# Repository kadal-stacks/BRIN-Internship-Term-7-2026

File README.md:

<!-- Official BRIN logo sourced from Wikimedia Commons; no AI-generated imagery is used. -->
<p align="center">
  
</p>

<h1 align="center">BRIN Internship | Term 7 · 2026</h1>

<p align="center">
  Catatan kerja dan hasil praktik di bidang embedded systems, firmware mikrokontroler, serta desain rangkaian dan PCB.
</p>

<p align="center">

</p>

---

## Tentang repositori

Repositori ini mengumpulkan pekerjaan teknis selama **Magang BRIN Term 7 (2026)**. Isinya berkembang melalui proyek KiCad untuk perancangan elektronik dan PCB, eksperimen program mikrokontroler, serta contoh firmware untuk latihan dan pengujian.

Struktur dibuat mengikuti kelompok pekerjaan agar file desain, source code, dan library pendukung tetap berada dekat dengan proyek masing-masing. Status setiap desain perlu dinilai dari file dan hasil verifikasi yang tersedia; keberadaan file proyek tidak otomatis berarti desain sudah tervalidasi atau siap fabrikasi.

## Ruang lingkup

### 1. Desain elektronik dan PCB dengan KiCad

| Folder | Isi |
| --- | --- |
| [`KiCAD/ATMega16-STM32 BP Adapter`](KiCAD/ATMega16-STM32%20BP%20Adapter) | Proyek adapter/pemetaan koneksi ATmega16 ke board STM32, dengan varian **SMD** dan **THT**. Berisi project, schematic, layout PCB, dan file pendukung yang tersedia. |
| [`KiCAD/Howland-VCCS`](KiCAD/Howland-VCCS) | Proyek rangkaian Howland Voltage-Controlled Current Source menggunakan TL072, dengan beberapa varian footprint/perakitan. |
| [`KiCAD/Impedance-meter2D_Main Board`](KiCAD/Impedance-meter2D_Main%20Board) | Folder proyek untuk main board impedance meter. Kelengkapan desain dapat berbeda dari proyek lainnya. |
| [`KiCAD/Part Lib/Kicad-STM32`](KiCAD/Part%20Lib/Kicad-STM32) | Library simbol, footprint, dan model 3D untuk modul STM32 **Blue Pill** dan **Black Pill**. Lihat README di dalam folder untuk rincian library. |
| [`KiCAD/Folder Tugas`](KiCAD/Folder%20Tugas) | Folder untuk materi/tugas KiCad. |

Format yang umum dijumpai antara lain `.kicad_pro` (project), `.kicad_sch` (schematic), `.kicad_pcb` (PCB layout), `.kicad_sym` (symbol library), dan `.kicad_mod` (footprint).

### 2. Firmware dan eksperimen mikrokontroler

| Lokasi | Isi |
| --- | --- |
| [`Program_MCU/AVR/AVR Atmega 328p - Arduino UNO R3`](Program_MCU/AVR/AVR%20Atmega%20328p%20-%20Arduino%20UNO%20R3) | Eksperimen pada ATmega328P/Arduino Uno R3, termasuk proyek ADC dan program LED non-blocking. |
| [`LED-Berjalan.cpp`](LED-Berjalan.cpp) | Contoh program LED berjalan. |
| [`Non-blocking using Multi LED.cpp`](Non-blocking%20using%20Multi%20LED.cpp) | Contoh pengaturan beberapa pola LED tanpa bergantung pada jeda blocking di loop utama. |

Sebagian proyek firmware memiliki `platformio.ini` dan dapat dibuka sebagai proyek PlatformIO. Untuk source code yang berdiri sendiri, pilih board, framework, pin, serta konfigurasi build yang sesuai sebelum mengompilasi.

## Deliverable PCB dan firmware terbaru

### PCB dengan paket Gerber dan gambar area

| Board | Luas outline | Dokumentasi |
| --- | ---: | --- |
| ATmega16–STM32 Adapter SMD | 1,450.75 mm² (14.5075 cm²) | [Gerber, drill, dan gambar area](KiCAD/ATMega16-STM32%20BP%20Adapter/ATMega16-STM32%20BP%20Adapter_SMD/README.md) |
| Howland VCCS TL072 THT | 3,506.24 mm² (35.0624 cm²) | [Gerber, drill, dan gambar area](KiCAD/Howland-VCCS/Howland-VCCS-TL072/README.md) |
| Howland VCCS TL072 SMD/hybrid | 618.85 mm² (6.1885 cm²) | [Gerber, drill, dan gambar area](KiCAD/Howland-VCCS/Howland-VCCS-TL072_SMD/Howland-VCCS-TL072_SMD/README.md) |

Luas dihitung dari outline `Edge.Cuts` pada file PCB sebagai rounded rectangle, bukan dari perkiraan visual. Board Raspberry Pi Zero Dev Board juga memiliki ukuran outline yang didokumentasikan, tetapi Gerber belum tersedia.

### Firmware AD9833

- [VCCS–AD9833 Frequency Controller (Arduino Nano)](Program_MCU/AVR/AVR%20Atmega%20328p%20-%20Arduino%20Nano/VCCS-AD9833%20Regulator/README.md)
- [Salinan di folder Arduino UNO R3](Program_MCU/AVR/AVR%20Atmega%20328p%20-%20Arduino%20UNO%20R3/VCCS%20-%20AD9833%20Regulator/README.md). Catatan: konfigurasi `platformio.ini` saat ini masih memilih board Nano.

## Alur kerja

Alur berikut merangkum cara menavigasi dan melanjutkan pekerjaan di repositori ini. Langkah verifikasi tetap perlu disesuaikan dengan proyek dan hardware yang digunakan.

1. **Pilih proyek yang relevan.** Buka folder di `KiCAD/` untuk pekerjaan desain atau `Program_MCU/` untuk eksperimen firmware.
2. **Buka file proyek utama.** Untuk KiCad, buka file `.kicad_pro` di folder proyek agar hubungan schematic, PCB, dan library lokal lebih mudah dipertahankan.
3. **Periksa keterkaitan desain.** Pastikan nomor pin, nama net, simbol, footprint, orientasi konektor, ukuran mekanik, dan tegangan logika sesuai datasheet serta modul fisik. Hal ini sangat penting untuk adapter ATmega16–STM32.
4. **Verifikasi sebelum menganggap selesai.** Tinjau Electrical Rules Checker (ERC) untuk schematic dan Design Rules Checker (DRC) untuk PCB. Periksa hasil simulasi atau pengujian firmware jika tersedia. ERC/DRC yang bersih sendiri tidak menjamin rangkaian bekerja pada hardware.
5. **Simpan perubahan secara terstruktur.** Pertahankan file yang dibutuhkan proyek, hindari memasukkan file lock atau file sementara editor, lalu commit perubahan dengan pesan yang menjelaskan lingkup pekerjaan.

## Referensi visual

Gambar di bawah merupakan tangkapan layar asli dari dokumentasi KiCad, digunakan sebagai referensi antarmuka schematic dan PCB editor, bukan sebagai klaim bahwa gambar tersebut adalah hasil desain proyek ini.

<p align="center">

</p>

## Galeri perangkat keras: foto referensi non-AI

Foto berikut berasal dari halaman produk/vendor atau aset foto yang sudah tersimpan di repository. Gambar membantu mengenali komponen, **bukan bukti bahwa board pada proyek ini sudah dirakit atau diuji**.

<p align="center">

</p>

<sub>Sumber foto: <a href="https://www.mikroe.com/atmega16">MikroE ATmega16</a>, aset <a href="KiCAD/Part%20Lib/Kicad-STM32/README.md">Blue Pill repository</a>, <a href="https://www.ti.com/product/TL072">TI TL072 / foto paket IC dari pemasok</a>, <a href="https://wholesale.pimoroni.com/en-eu/products/adafruit-bmp280-i2c-or-spi-barometric-pressure-altitude-sensor">modul BMP280 dari pemasok</a>, dan <a href="https://laelectronica.com.gt/arduino-uno-rev3">foto Arduino Uno R3</a>. Foto TL072 yang ditampilkan adalah paket DIP-8; periksa footprint proyek sebelum membeli komponen.</sub>

## Memulai

- **KiCad:** instal KiCad, lalu buka file `.kicad_pro` dari folder proyek yang akan dikerjakan.
- **Firmware:** untuk proyek yang memiliki `platformio.ini`, gunakan VS Code dengan ekstensi PlatformIO atau PlatformIO CLI. Pastikan board/framework cocok dengan konfigurasi proyek.
- **Hardware:** sebelum upload firmware atau memberi daya, cocokkan wiring dan level tegangan dengan datasheet serta lakukan pemeriksaan dasar untuk menghindari kerusakan komponen.

## Catatan status dan akurasi

Repositori ini merupakan arsip kerja yang berkembang. Skema, mapping pin, footprint, routing, pengaturan panel, dan source code perlu diverifikasi terhadap versi tool, datasheet komponen, hardware aktual, serta persyaratan manufaktur. Jangan menganggap desain siap produksi hanya berdasarkan visual layout atau status file yang sudah di-commit.

## Sumber gambar dan aset

- **Logo BRIN:** karya resmi Badan Riset dan Inovasi Nasional; ditautkan dari [Wikimedia Commons](https://commons.wikimedia.org/wiki/File:LOGO_BRIN_NEW.jpg), yang mencatat sumber dan status domain publik di Indonesia.
- **Tangkapan layar KiCad:** [KiCad 8 release article](https://www.kicad.org/blog/2024/02/Version-8.0.0-Released/) dan [dokumentasi PCB Editor KiCad](https://docs.kicad.org/9.0/it/pcbnew/pcbnew.html).
- **Library STM32:** lihat [README library lokal](KiCAD/Part%20Lib/Kicad-STM32/README.md) untuk detail simbol, footprint, model 3D, dan konteks sumbernya.

<p align="center">
  <sub>Logo BRIN digunakan untuk menunjukkan konteks kegiatan magang. Repositori ini tidak menyatakan dirinya sebagai repositori resmi BRIN.</sub>
</p>

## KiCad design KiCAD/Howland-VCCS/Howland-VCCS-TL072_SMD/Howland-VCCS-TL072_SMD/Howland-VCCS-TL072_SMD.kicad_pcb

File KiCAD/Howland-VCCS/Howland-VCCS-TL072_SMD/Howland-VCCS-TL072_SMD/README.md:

<p align="center">
  
</p>

# Howland VCCS with TL072 (SMD / Hybrid)

Project KiCad untuk varian Howland VCCS dengan jaringan resistor SMD 0805. Schematic terbaru berbeda dari revisi lama: kini memakai R1–R4 = 100 kΩ, R5 = 150 Ω, dan RV1 = 1 kΩ.

## Komponen dari schematic

| Ref. | Komponen | Nilai / footprint |
| --- | --- | --- |
| U1 | Dual op-amp TL072 | **DIP-8 THT** |
| R1–R4 | Resistor | 100 kΩ, SMD 0805 |
| R5 | Resistor | 150 Ω, SMD 0805 |
| RV1 | Potensiometer trimmer | 1 kΩ, Bourns 3296W vertical THT |
| J4 | Pin header 1×6 | Pitch 2.54 mm, THT |
| H1–H2 | Mounting hole | M2.2 / M2 |
| Net labels | Id+, Id-, Out | Label antarmuka sinyal |

Desain ini **hybrid**, bukan full-SMD, karena U1, RV1, dan J4 masih memakai footprint through-hole. Schematic yang terbaru tidak lagi menunjukkan R6/R7, C1/C2, atau solder jumper JP1/JP2 yang tercantum di dokumentasi versi sebelumnya.

Secara fungsi, topologi Howland ditujukan untuk menghasilkan arus beban yang dikendalikan sinyal tegangan. Rasio resistor dan toleransinya mempengaruhi akurasi. Verifikasi supply VCC/VEE, swing output TL072, compliance voltage, dan koneksi beban sebelum uji.

## Dimensi dan luas board

| Parameter | Nilai |
| --- | ---: |
| Lebar bounding outline | 27.078 mm |
| Tinggi bounding outline | 22.886 mm |
| Radius sudut | 1.00 mm |
| Luas bounding rectangle | 619.71 mm² |
| Koreksi empat sudut membulat | 0.86 mm² |
| **Luas bidang PCB aktual** | **618.85 mm²** |
| **Konversi** | **6.1885 cm²** |

Luas dihitung dari rounded outline pada layer `Edge.Cuts` menggunakan `A = W × H − (4 − π)r²`.

## Paket Gerber dan drill

**Status: Gerber dan drill tersedia.**

[Unduh paket Gerber ZIP](Howland-VCCS-TL072-SMD-Gerber.zip)

Layer individual:
- Copper: [F_Cu](Howland-VCCS-TL072_SMD-F_Cu.gbr), [B_Cu](Howland-VCCS-TL072_SMD-B_Cu.gbr)
- Solder mask: [F_Mask](Howland-VCCS-TL072_SMD-F_Mask.gbr), [B_Mask](Howland-VCCS-TL072_SMD-B_Mask.gbr)
- Paste: [F_Paste](Howland-VCCS-TL072_SMD-F_Paste.gbr), [B_Paste](Howland-VCCS-TL072_SMD-B_Paste.gbr)
- Silkscreen: [F_Silkscreen](Howland-VCCS-TL072_SMD-F_Silkscreen.gbr), [B_Silkscreen](Howland-VCCS-TL072_SMD-B_Silkscreen.gbr)
- Board profile: [Edge_Cuts](Howland-VCCS-TL072_SMD-Edge_Cuts.gbr)
- Drill: [PTH](Howland-VCCS-TL072_SMD-PTH.drl), [NPTH](Howland-VCCS-TL072_SMD-NPTH.drl)
- Job metadata: [Gerber job](Howland-VCCS-TL072_SMD-job.gbrjob)

Gerber dibuat dengan KiCad 10.0.5 pada 13 November 2026.

## File project

- `Howland-VCCS-TL072_SMD.kicad_pro`
- `Howland-VCCS-TL072_SMD.kicad_sch`
- `Howland-VCCS-TL072_SMD.kicad_pcb`

Sebelum fabrikasi, pastikan nilai/footprint sesuai schematic terbaru, khususnya footprint U1 DIP-8 dan trimmer THT. Jalankan ERC/DRC lagi apabila ada perubahan schematic, footprint, atau layout.

---

[README varian parent](../README.md) · [README Howland VCCS](../../README.md)

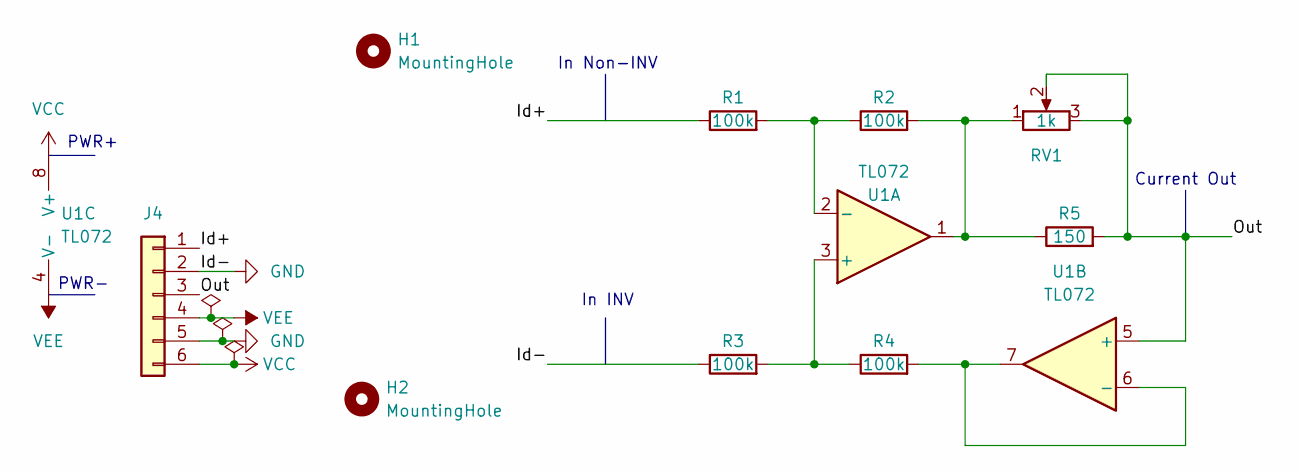
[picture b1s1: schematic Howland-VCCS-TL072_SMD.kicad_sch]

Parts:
H1, H2: MountingHole; MountingHole_2.2mm_M2
J4: Conn_01x06; PinHeader_1x06_P2.54mm_Vertical
R1, R2, R3, R4: 100k; R_0805_2012Metric
R5: 150; R_0805_2012Metric
RV1: 1k; Potentiometer_Bourns_3296W_Vertical
U1: TL072; DIP-8_W7.62mm

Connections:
/Id+: J4.1, R1.1
/Out: J4.3, R5.2, RV1.2, RV1.3, U1.5 (+)
GND: J4.2, J4.5, R3.1
unnamed: R2.2, R5.1, RV1.1, U1.1
unnamed: R3.2, R4.1, U1.3 (+)
unnamed: R1.2, R2.1, U1.2 (-)
unnamed: R4.2, U1.6 (-), U1.7
VCC: J4.6, U1.8 (V+)
VEE: J4.4, U1.4 (V-)

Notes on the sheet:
In INV
In Non-INV
PWR-
Current Out
PWR+

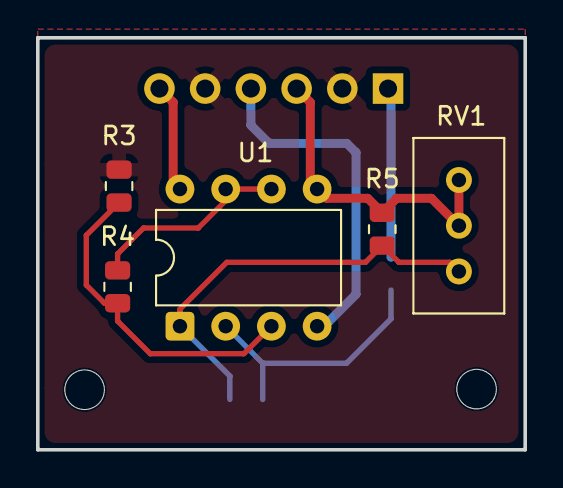
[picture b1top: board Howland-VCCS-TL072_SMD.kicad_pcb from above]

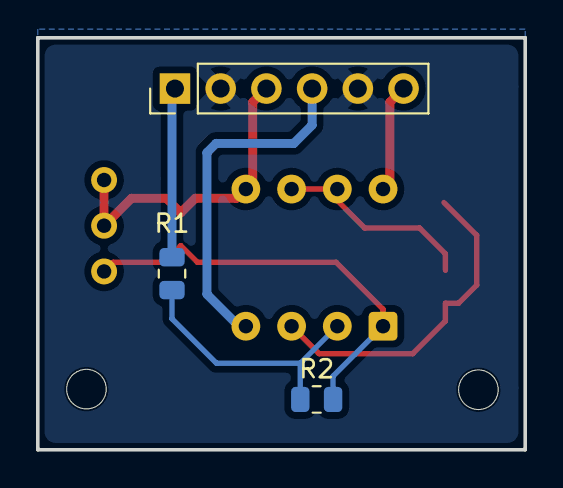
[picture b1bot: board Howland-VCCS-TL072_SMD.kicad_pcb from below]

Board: 2 copper layers, 27.1 x 22.9 mm, 10 parts (3 on the bottom side), 9 nets.

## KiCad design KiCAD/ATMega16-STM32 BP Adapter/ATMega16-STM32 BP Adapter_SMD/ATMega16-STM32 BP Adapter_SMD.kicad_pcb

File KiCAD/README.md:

<table align="center">
  <tr>
    <td align="center" valign="middle" width="33%">
      
    </td>
    <td align="center" valign="middle" width="33%">
      
    </td>
    <td align="center" valign="middle" width="33%">
      
    </td>
  </tr>
</table>
<p align="center"><sub>STM32 Blue Pill / Black Pill reference · Arm Cortex core depends on the exact MCU variant</sub></p>

# KiCad Projects

Folder ini menampung schematic, PCB layout, library komponen, dan paket manufaktur dari proyek instrumentasi selama magang.

## Proyek

| Proyek | Fungsi | Status file manufaktur | Area outline PCB |
| --- | --- | --- | ---: |
| [ATmega16–STM32 Adapter (SMD)](ATMega16-STM32%20BP%20Adapter/ATMega16-STM32%20BP%20Adapter_SMD/README.md) | Breakout dan routing pin ATmega16 ke header STM32 | Gerber + drill tersedia | **1,450.75 mm² / 14.5075 cm²** |
| [Howland VCCS TL072 (THT)](Howland-VCCS/Howland-VCCS-TL072/README.md) | Voltage-controlled current source berbasis TL072 | Gerber + drill tersedia | **3,506.24 mm² / 35.0624 cm²** |
| [Howland VCCS TL072 (SMD/hybrid)](Howland-VCCS/Howland-VCCS-TL072_SMD/Howland-VCCS-TL072_SMD/README.md) | Varian Howland dengan resistor SMD dan IC/op-amp THT | Gerber + drill tersedia | **618.85 mm² / 6.1885 cm²** |
| [Impedance Meter Main Board](Impedance-meter2D_Main%20Board/README.md) | Workspace main board impedance meter | File manufaktur belum tersedia di folder | Belum dihitung |
| [Part Libraries](Part%20Lib/README.md) | Symbol, footprint, dan model 3D | Library | — |
| [Raspberry Pi Zero Dev Board](RaspiZeroDevBoard/README.md) | Carrier board Raspberry Pi Zero dengan ADC eksternal, RTC, interface serial, RS-485, LCD, dan rail daya | PCB tersedia; Gerber belum ada | **19,581.96 mm² / 195.8196 cm²** |
| [VCCS 2 Buffer](Howland-VCCS/VCCS%202%20Buffer/README.md) | Workspace schematic buffer berbasis AD826ANZ dan TL082 | PCB masih stub; Gerber/area belum tersedia | Belum dihitung |

### Area board yang sudah dihitung

Dimensi diambil dari geometri `Edge.Cuts` pada file PCB dan dicocokkan dengan layer Gerber profile. Ketiga outline berbentuk persegi panjang dengan empat sudut membulat. Area dihitung sebagai:

`A = (W × H) − (4 − π)r²`

dengan `W` dan `H` sebagai ukuran bounding rectangle dan `r` sebagai radius sudut. Nilai ini adalah luas bidang outline PCB, bukan luas komponen atau bounding box tanpa koreksi sudut.

## Workflow manufaktur KiCad

1. Buka file `.kicad_pro` dari folder proyek.
2. Validasi schematic, footprint, nomor pad, konektor, dan net.
3. Jalankan ERC untuk schematic dan DRC untuk PCB.
4. Plot layer Gerber yang diperlukan dan generate file drill PTH/NPTH.
5. Periksa file `Edge_Cuts.gbr`, `*.gbrjob`, dan arsip ZIP sebelum dikirim ke manufaktur.

Paket Gerber yang tersedia ditautkan dari README masing-masing proyek. Jangan menggunakan file dari folder atau revisi berbeda sebagai satu paket produksi.

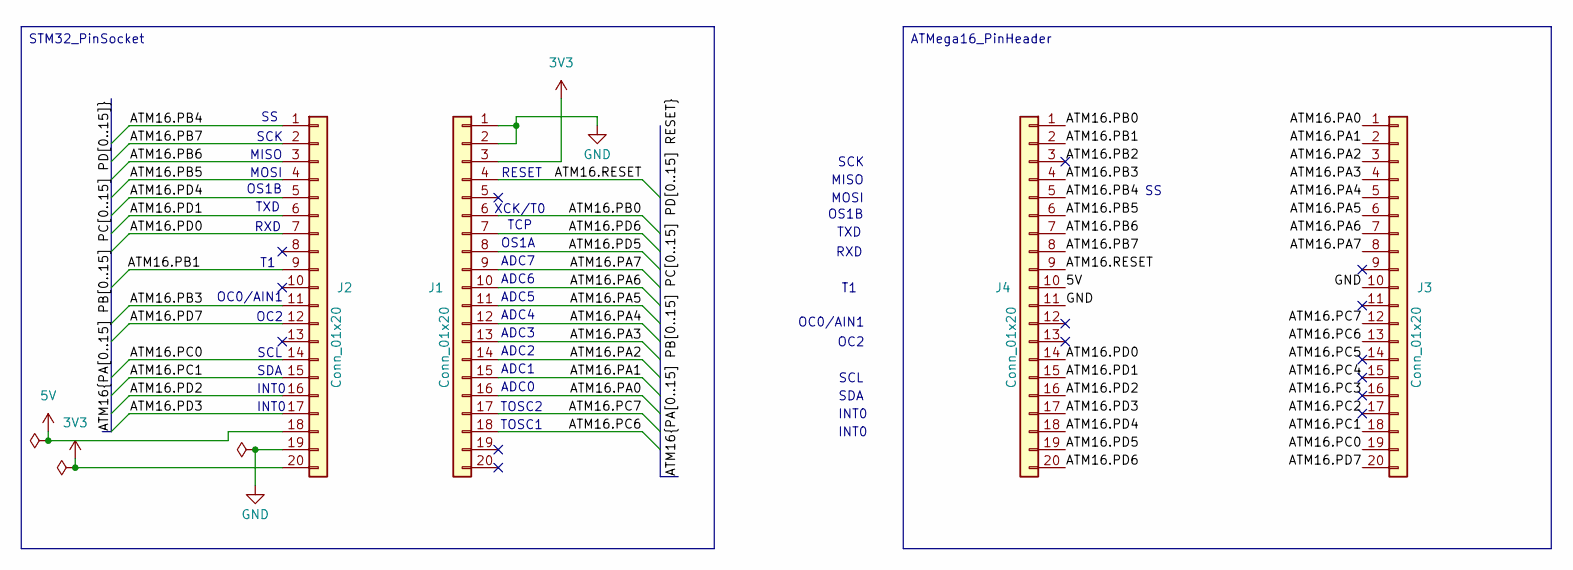
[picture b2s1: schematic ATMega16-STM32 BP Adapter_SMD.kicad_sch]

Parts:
J1: Conn_01x20; PinSocket_1x20_P2.54mm_Vertical_SMD_Pin1Right
J2: Conn_01x20; PinSocket_1x20_P2.54mm_Vertical_SMD_Pin1Left
J3: Conn_01x20; PinHeader_1x20_P2.54mm_Vertical_SMD_Pin1Right
J4: Conn_01x20; PinHeader_1x20_P2.54mm_Vertical_SMD_Pin1Left

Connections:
3V3: J1.3, J2.20
5V: J2.18, J4.10
/ATM16.PA0: J1.16, J3.1
/ATM16.PA1: J1.15, J3.2
/ATM16.PA2: J1.14, J3.3
/ATM16.PA3: J1.13, J3.4
/ATM16.PA4: J1.12, J3.5
/ATM16.PA5: J1.11, J3.6
/ATM16.PA6: J1.10, J3.7
/ATM16.PA7: J1.9, J3.8
/ATM16.PB0: J1.6, J4.1
/ATM16.PB1: J2.9, J4.2
/ATM16.PB2: J4.3
/ATM16.PB3: J2.11, J4.4
/ATM16.PB4: J2.1, J4.5
/ATM16.PB5: J2.4, J4.6
/ATM16.PB6: J2.3, J4.7
/ATM16.PB7: J2.2, J4.8
/ATM16.PC0: J2.14, J3.19
/ATM16.PC1: J2.15, J3.18
/ATM16.PC2: J3.17
/ATM16.PC3: J3.16
/ATM16.PC4: J3.15
/ATM16.PC5: J3.14
/ATM16.PC6: J1.18, J3.13
/ATM16.PC7: J1.17, J3.12
/ATM16.PD0: J2.7, J4.14
/ATM16.PD1: J2.6, J4.15
/ATM16.PD2: J2.16, J4.16
/ATM16.PD3: J2.17, J4.17
/ATM16.PD4: J2.5, J4.18
/ATM16.PD5: J1.8, J4.19
/ATM16.PD6: J1.7, J4.20
/ATM16.PD7: J2.12, J3.20
/ATM16.RESET: J1.4, J4.9
GND: J1.1, J1.2, J2.19, J3.10, J4.11

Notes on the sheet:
OC2
INT0
SCK
RXD
ADC7
RESET
OC0/AIN1
SDA
ADC1
ADC2
SCL
MOSI
TXD
TOSC2
ADC4
OS1A
OS1B
TOSC1
TCP
XCK/T0
MISO
ADC6
ADC5
ADC3
ADC0
ATMega16_PinHeader
STM32_PinSocket

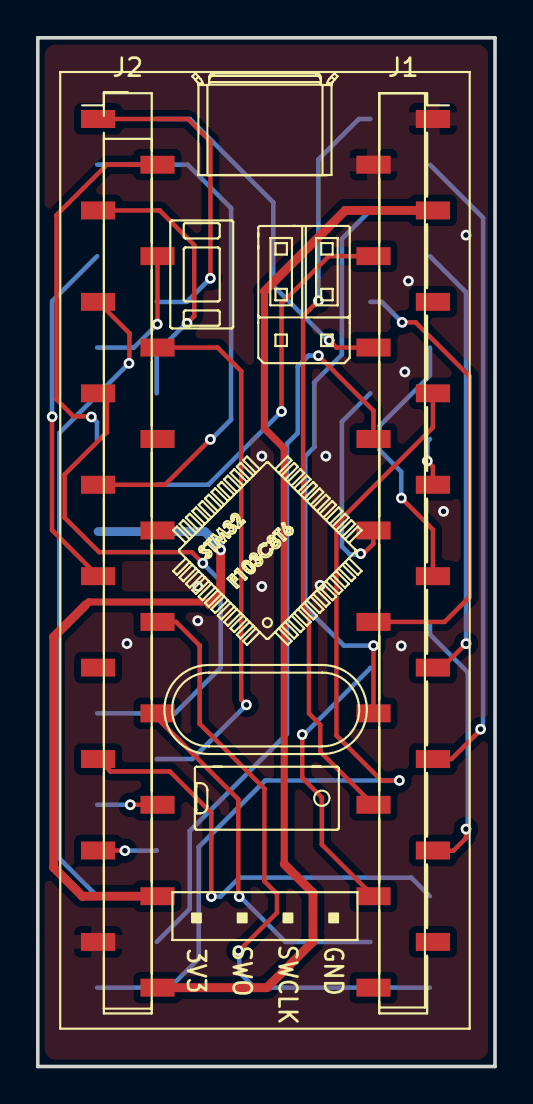
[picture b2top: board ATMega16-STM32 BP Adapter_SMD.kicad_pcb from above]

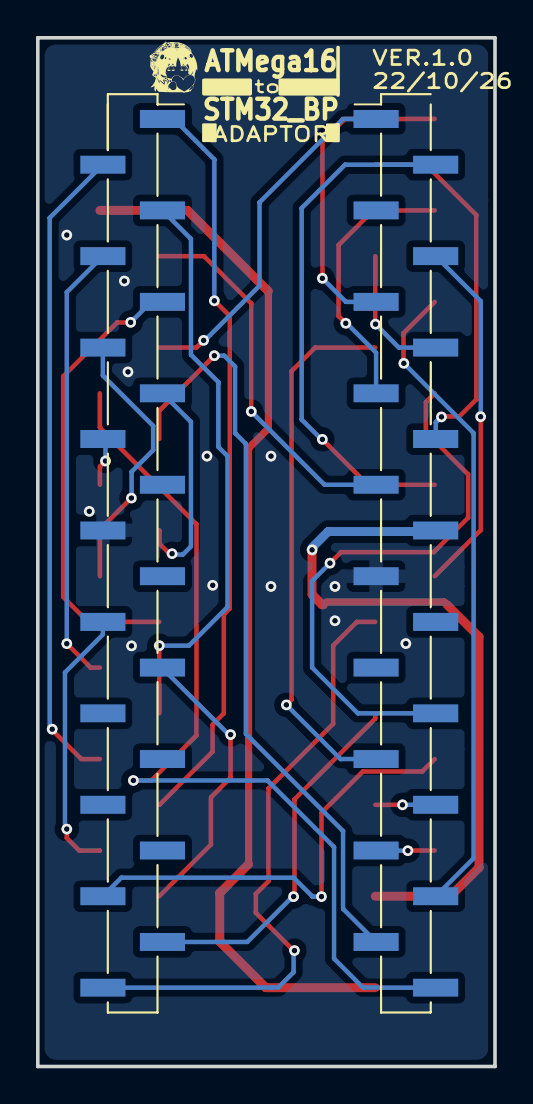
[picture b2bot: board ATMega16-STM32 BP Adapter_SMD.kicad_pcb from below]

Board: 2 copper layers, 25.4 x 57.1 mm, 5 parts (2 on the bottom side), 31 nets.

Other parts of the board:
U2: YAAJ_BluePill_Part_Like; BLUEPILL_SILKSCREEN

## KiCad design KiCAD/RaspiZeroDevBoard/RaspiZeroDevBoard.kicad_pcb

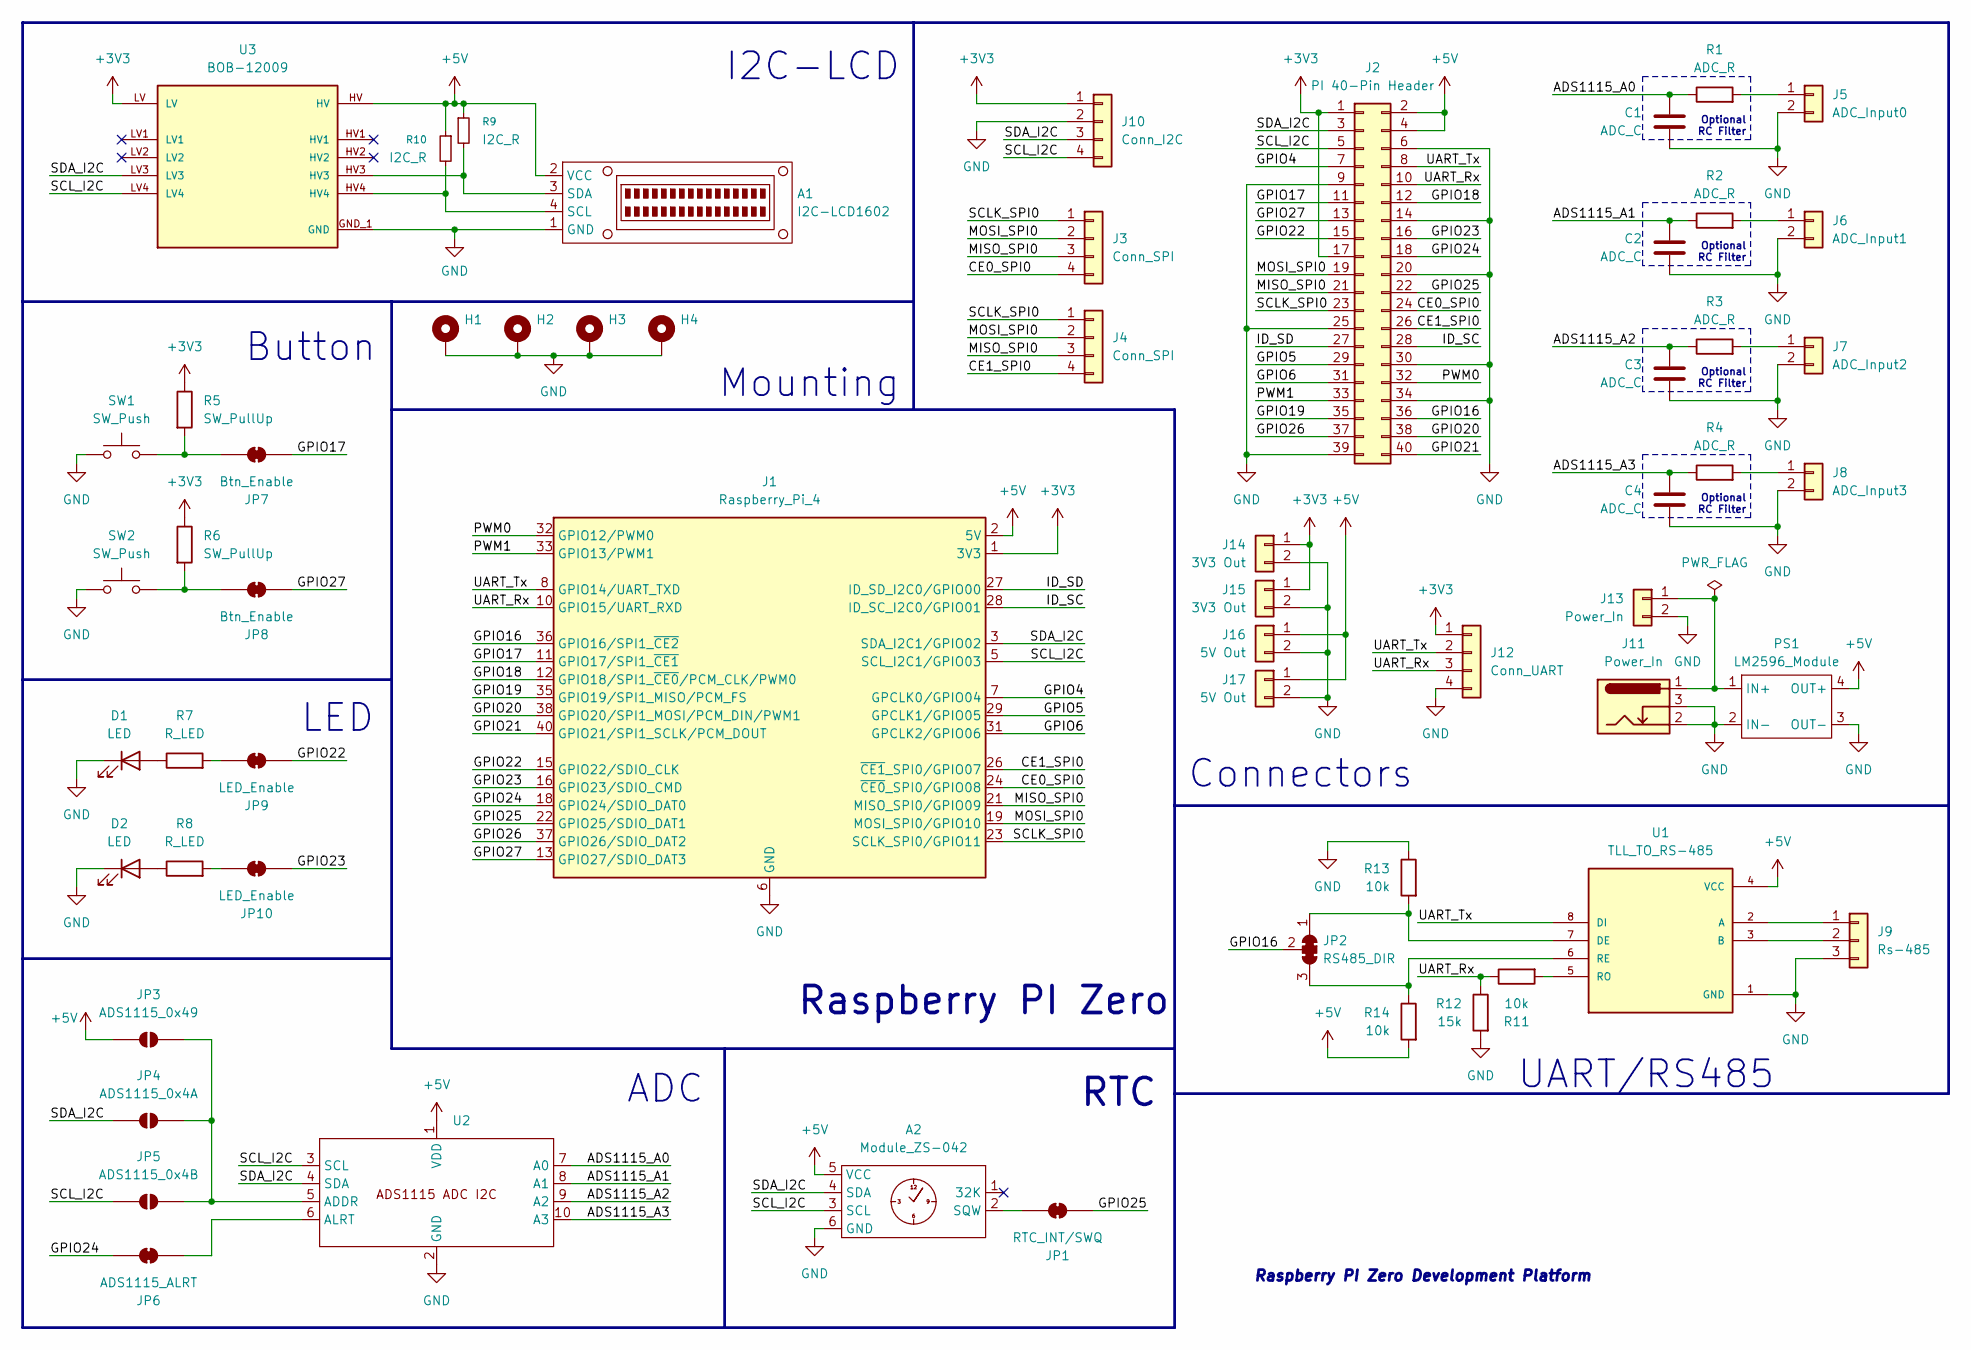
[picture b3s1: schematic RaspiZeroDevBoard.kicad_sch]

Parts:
A1: I2C-LCD1602; MODULE_LCD-16X2
A2: Module_ZS-042; MODULE_DS3231
C1, C2, C3, C4: ADC_C; C_0603_1608Metric
D1, D2: LED; LED_D5.0mm
H1, H2, H3, H4: MountingHole_Pad; MountingHole_2.2mm_M2
J1: Raspberry_Pi_4; Raspberry_Pi_Zero_Socketed_THT_FaceDown_MountingHoles
J2: PI 40-Pin Header; PinHeader_2x20_P2.54mm_Vertical
J3, J4: Conn_SPI; Molex_KK-254_AE-6410-04A_1x04_P2.54mm_Vertical
J5: ADC_Input0; Molex_KK-254_AE-6410-02A_1x02_P2.54mm_Vertical
J6: ADC_Input1; Molex_KK-254_AE-6410-02A_1x02_P2.54mm_Vertical
J7: ADC_Input2; Molex_KK-254_AE-6410-02A_1x02_P2.54mm_Vertical
J8: ADC_Input3; Molex_KK-254_AE-6410-02A_1x02_P2.54mm_Vertical
J9: Rs-485; Molex_KK-254_AE-6410-03A_1x03_P2.54mm_Vertical
J10: Conn_I2C; Molex_KK-254_AE-6410-04A_1x04_P2.54mm_Vertical
J11: Power_In; BarrelJack_Horizontal
J12: Conn_UART; Molex_KK-254_AE-6410-04A_1x04_P2.54mm_Vertical
J13: Power_In; Molex_KK-254_AE-6410-02A_1x02_P2.54mm_Vertical
J14, J15: 3V3 Out; Molex_KK-254_AE-6410-02A_1x02_P2.54mm_Vertical
J16, J17: 5V Out; Molex_KK-254_AE-6410-02A_1x02_P2.54mm_Vertical
JP1: RTC_INT/SWQ; SolderJumper-2_P1.3mm_Bridged_RoundedPad1.0x1.5mm
JP2: RS485_DIR; SolderJumper-3_P1.3mm_Bridged123_RoundedPad1.0x1.5mm
JP3: ADS1115_0x49; SolderJumper-2_P1.3mm_Open_RoundedPad1.0x1.5mm
JP4: ADS1115_0x4A; SolderJumper-2_P1.3mm_Open_RoundedPad1.0x1.5mm
JP5: ADS1115_0x4B; SolderJumper-2_P1.3mm_Open_RoundedPad1.0x1.5mm
JP6: ADS1115_ALRT; SolderJumper-2_P1.3mm_Bridged_RoundedPad1.0x1.5mm
JP7, JP8: Btn_Enable; SolderJumper-2_P1.3mm_Bridged_RoundedPad1.0x1.5mm
JP9, JP10: LED_Enable; SolderJumper-2_P1.3mm_Bridged_RoundedPad1.0x1.5mm
PS1: LM2596_Module; LM2596-DC-DC
R1, R2, R3, R4: ADC_R; R_0603_1608Metric
R5, R6: SW_PullUp; R_0603_1608Metric
R7, R8: R_LED; R_0603_1608Metric
R9, R10: I2C_R; R_0603_1608Metric
R11, R13, R14: 10k; R_0603_1608Metric
R12: 15k; R_0603_1608Metric
SW1, SW2: SW_Push; SW_PUSH_6mm_H5mm
U1: TLL_TO_RS-485; MODULE_MAX485_MODULE_5V_LOGIC_TLL_TO_RS-485_CONVERTER; PARTREV 1r0
U2: Modul_ADS1115_ADC_I2C
U3: BOB-12009; CONV_BOB-12009; PARTREV 01

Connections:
+3V3: J1.1 (3V3), J1.17 (3V3), J2.1, J2.17, J10.1, J12.1, J14.1, J15.1, R5.1, R6.1, U3.LV
+5V: A1.2 (VCC), A2.5 (VCC), J1.2 (5V), J1.4 (5V), J2.2, J2.4, J16.1, J17.1, JP3.1 (A), PS1.4 (OUT+), R9.1, R10.1, R14.2, U1.4 (VCC), U2.1 (VDD), U3.HV
/ADS1115_A0: C1.1, R1.1, U2.7 (A0)
/ADS1115_A1: C2.1, R2.1, U2.8 (A1)
/ADS1115_A2: C3.1, R3.1, U2.9 (A2)
/ADS1115_A3: C4.1, R4.1, U2.10 (A3)
/CE0_SPI0: J1.24 (~CE0_SPI0/GPIO08), J2.24, J3.4
/CE1_SPI0: J1.26 (~CE1_SPI0/GPIO07), J2.26, J4.4
/GPIO4: J1.7 (GPCLK0/GPIO04), J2.7
/GPIO5: J1.29 (GPCLK1/GPIO05), J2.29
/GPIO6: J1.31 (GPCLK2/GPIO06), J2.31
/GPIO16: J1.36 (GPIO16/SPI1_~CE2), J2.36, JP2.2 (C)
/GPIO17: J1.11 (GPIO17/SPI1_~CE1), J2.11, JP7.2 (B)
/GPIO18: J1.12 (GPIO18/SPI1_~CE0/PCM_CLK/PWM0), J2.12
/GPIO19: J1.35 (GPIO19/SPI1_MISO/PCM_FS), J2.35
/GPIO20: J1.38 (GPIO20/SPI1_MOSI/PCM_DIN/PWM1), J2.38
/GPIO21: J1.40 (GPIO21/SPI1_SCLK/PCM_DOUT), J2.40
/GPIO22: J1.15 (GPIO22/SDIO_CLK), J2.15, JP9.2 (B)
/GPIO23: J1.16 (GPIO23/SDIO_CMD), J2.16, JP10.2 (B)
/GPIO24: J1.18 (GPIO24/SDIO_DAT0), J2.18, JP6.1 (A)
/GPIO25: J1.22 (GPIO25/SDIO_DAT1), J2.22, JP1.2 (B)
/GPIO26: J1.37 (GPIO26/SDIO_DAT2), J2.37
/GPIO27: J1.13 (GPIO27/SDIO_DAT3), J2.13, JP8.2 (B)
/ID_SC: J1.28 (ID_SC_I2C0/GPIO01), J2.28
/ID_SD: J1.27 (ID_SD_I2C0/GPIO00), J2.27
/MISO_SPI0: J1.21 (MISO_SPI0/GPIO09), J2.21, J3.3, J4.3
/MOSI_SPI0: J1.19 (MOSI_SPI0/GPIO10), J2.19, J3.2, J4.2
/PWM0: J1.32 (GPIO12/PWM0), J2.32
/PWM1: J1.33 (GPIO13/PWM1), J2.33
/SCLK_SPI0: J1.23 (SCLK_SPI0/GPIO11), J2.23, J3.1, J4.1
/SCL_I2C: A2.3 (SCL), J1.5 (SCL_I2C1/GPIO03), J2.5, J10.4, JP5.1 (A), U2.3 (SCL), U3.LV4
/SDA_I2C: A2.4 (SDA), J1.3 (SDA_I2C1/GPIO02), J2.3, J10.3, JP4.1 (A), U2.4 (SDA), U3.LV3
/UART_Rx: J1.10 (GPIO15/UART_RXD), J2.10, J12.3, R11.1, R12.1
/UART_Tx: J1.8 (GPIO14/UART_TXD), J2.8, J12.2, U1.8 (DI)
GND: A1.1 (GND), A2.6 (GND), C1.2, C2.2, C3.2, C4.2, D1.1 (K), D2.1 (K), H1.1, H2.1, H3.1, H4.1, J1.6 (GND), J1.9 (GND), J1.14 (GND), J1.20 (GND), J1.25 (GND), J1.30 (GND), J1.34 (GND), J1.39 (GND), J2.6, J2.9, J2.14, J2.20, J2.25, J2.30, J2.34, J2.39, J5.2, J6.2, J7.2, J8.2, J9.3, J10.2, J11.2, J11.3, J12.4, J13.2, J14.2, J15.2, J16.2, J17.2, PS1.2 (IN-), PS1.3 (OUT-), R12.2, R13.1, SW1.1, SW2.1, U1.1 (GND), U2.2 (GND), U3.GND_1 (GND), U3.GND_2 (GND)
unnamed: A1.4 (SCL), R10.2, U3.HV4
unnamed: A1.3 (SDA), R9.2, U3.HV3
unnamed: A2.2 (SQW), JP1.1 (A)
unnamed: D1.2 (A), R7.1
unnamed: D2.2 (A), R8.1
unnamed: J5.1, R1.2
unnamed: J6.1, R2.2
unnamed: J7.1, R3.2
unnamed: J8.1, R4.2
unnamed: J9.1, U1.2 (A)
unnamed: J9.2, U1.3 (B)
unnamed: J11.1, J13.1, PS1.1 (IN+)
unnamed: JP2.1 (A), R13.2, U1.7 (DE)
unnamed: JP2.3 (B), R14.1, U1.6 (RE)
unnamed: JP3.2 (B), JP4.2 (B), JP5.2 (B), U2.5 (ADDR)
unnamed: JP6.2 (B), U2.6 (ALRT)
unnamed: JP7.1 (A), R5.2, SW1.2
unnamed: JP8.1 (A), R6.2, SW2.2
unnamed: JP9.1 (A), R7.2
unnamed: JP10.1 (A), R8.2
unnamed: R11.2, U1.5 (RO)

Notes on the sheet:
ADC
Optional RC Filter
RTC
Mounting
Raspberry PI Zero
Raspberry PI Zero Development Platform
Connectors
LED
Button
UART/RS485
I2C-LCD

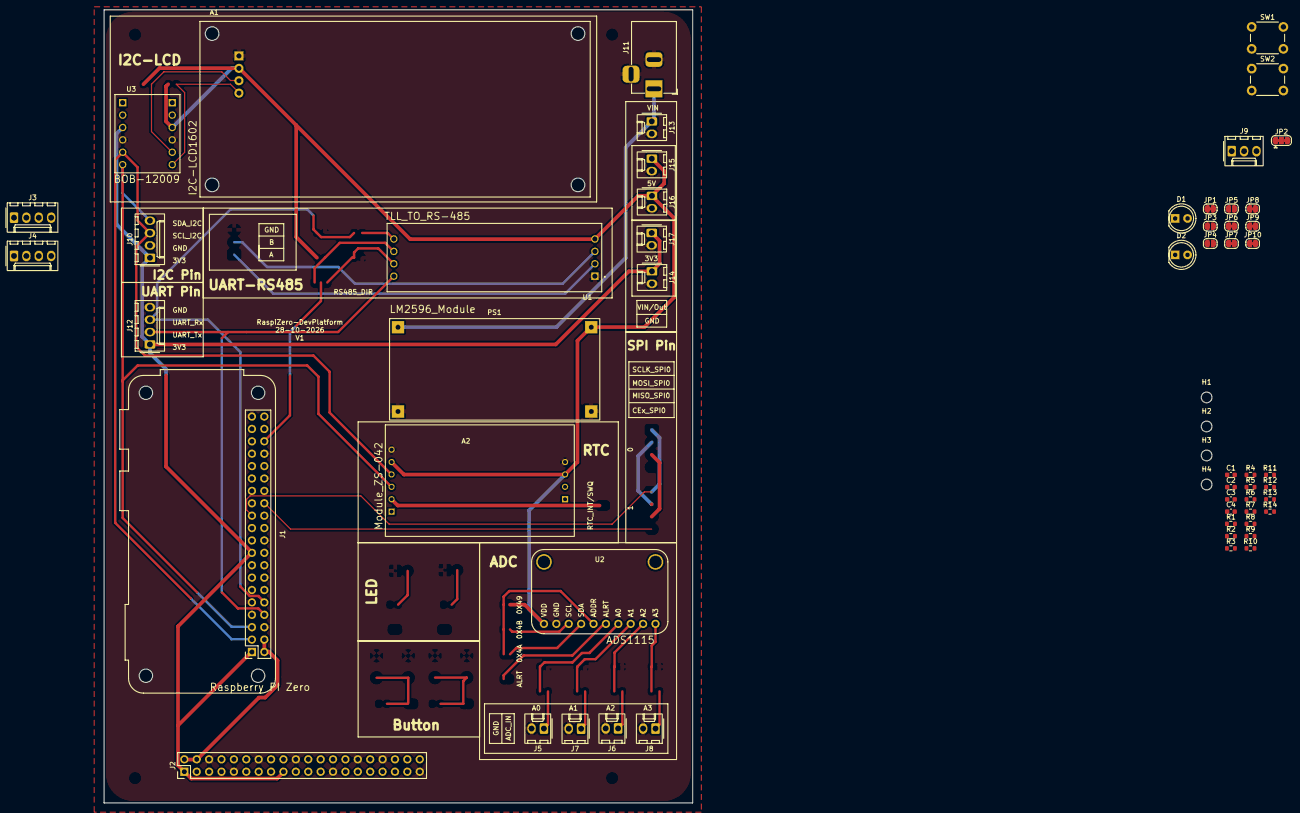
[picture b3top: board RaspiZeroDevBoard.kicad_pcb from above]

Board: 2 copper layers, 120.6 x 162.6 mm, 59 parts (0 on the bottom side), 56 nets.

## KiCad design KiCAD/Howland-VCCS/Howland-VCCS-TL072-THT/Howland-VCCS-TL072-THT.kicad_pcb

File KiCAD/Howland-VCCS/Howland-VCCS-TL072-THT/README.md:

# Howland VCCS with TL072 (THT)

Varian THT dari rangkaian Howland Voltage-Controlled Current Source. Komponen yang tertera: U1 TL072 dengan footprint DIP-8, empat resistor 100 kΩ (R1–R4), R5 150 Ω, RV1 1 kΩ, dua header 1×3 (J1/J2), serta rail VCC/VEE/GND.

<p align="center"></p><sub>Foto IC TL072 DIP-8 dari pemasok; lihat <a href="https://www.ti.com/product/TL072">datasheet resmi TI</a> untuk package/pinout. Bukan foto board Howland yang dirancang di repository.</sub>

## Fungsi
Jaringan resistor dan umpan balik TL072 dimaksudkan untuk mengendalikan arus beban berdasarkan sinyal kendali. Rasio resistor, setelan RV1, supply, dan tegangan compliance menentukan hasil nyata.

## Verifikasi
Buka file project, periksa pinout serta label konektor Id+/Id-/Out, jalankan ERC/DRC, dan pastikan footprint DIP-8, diameter drill, resistor THT, serta jarak komponen sesuai perakitan. Validasi dengan simulasi dan pengukuran arus pada beberapa beban sebelum menganggapnya final.

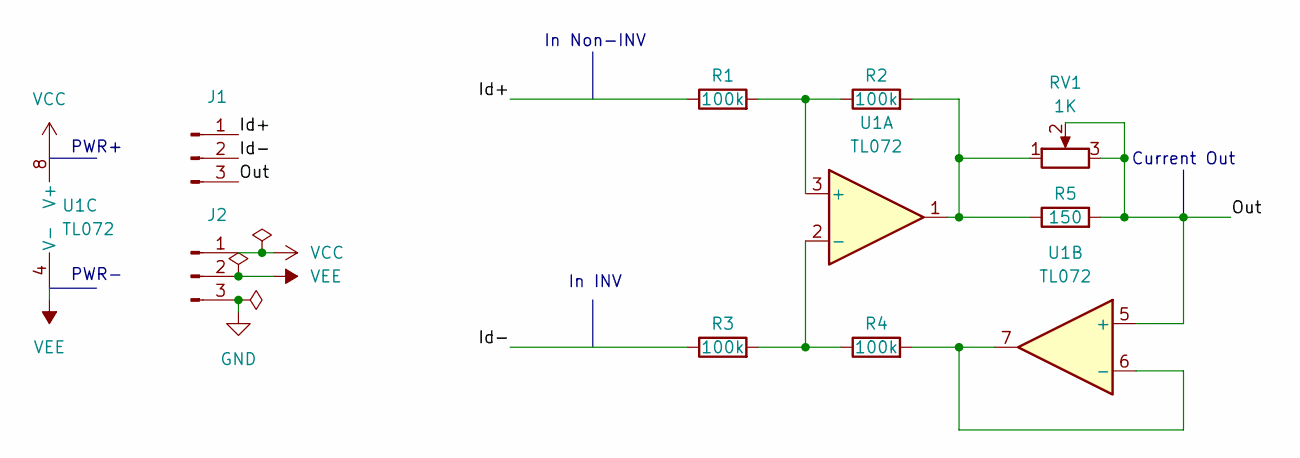
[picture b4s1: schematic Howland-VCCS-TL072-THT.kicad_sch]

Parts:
J1, J2: Conn_01x03_Pin; PinHeader_1x03_P2.54mm_Vertical
R1, R2, R3, R4: 100k; R_Axial_DIN0207_L6.3mm_D2.5mm_P10.16mm_Horizontal
R5: 150; R_Axial_DIN0207_L6.3mm_D2.5mm_P10.16mm_Horizontal
RV1: 1K; Potentiometer_Bourns_3296W_Vertical
U1: TL072; DIP-8_W7.62mm

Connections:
/Id+: J1.1, R1.1
/Id-: J1.2, R3.1
/Out: J1.3, R5.2, RV1.2, RV1.3, U1.5 (+)
GND: J2.3
unnamed: R2.2, R5.1, RV1.1, U1.1
unnamed: R1.2, R2.1, U1.3 (+)
unnamed: R3.2, R4.1, U1.2 (-)
unnamed: R4.2, U1.6 (-), U1.7
VCC: J2.1, U1.8 (V+)
VEE: J2.2, U1.4 (V-)

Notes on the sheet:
PWR+
In INV
In Non-INV
PWR-
Current Out

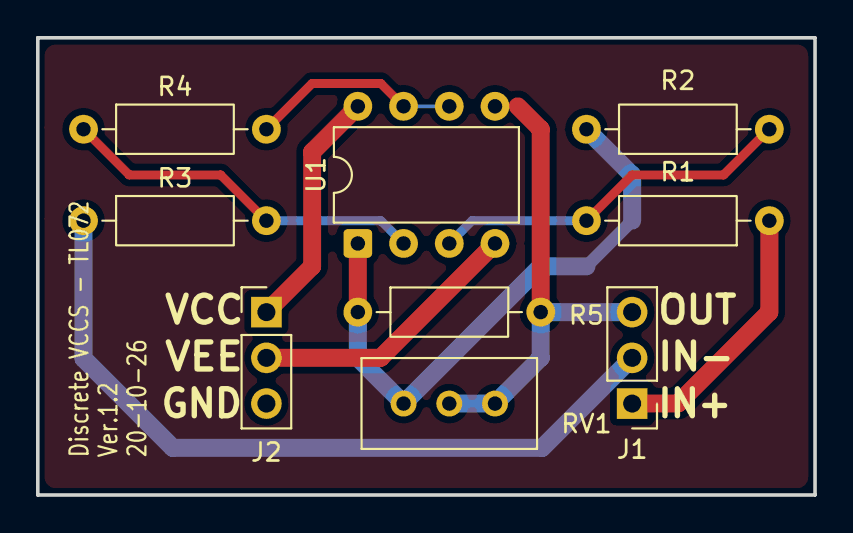
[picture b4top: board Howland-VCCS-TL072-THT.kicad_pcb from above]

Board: 2 copper layers, 43.2 x 25.4 mm, 9 parts (0 on the bottom side), 9 nets.
